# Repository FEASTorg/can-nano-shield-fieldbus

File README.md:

# can-nano-shield

A compact Arduino Nano shield with MCP2515 & TJA1051/3 for easy CAN bus integration. Work-in-progress.

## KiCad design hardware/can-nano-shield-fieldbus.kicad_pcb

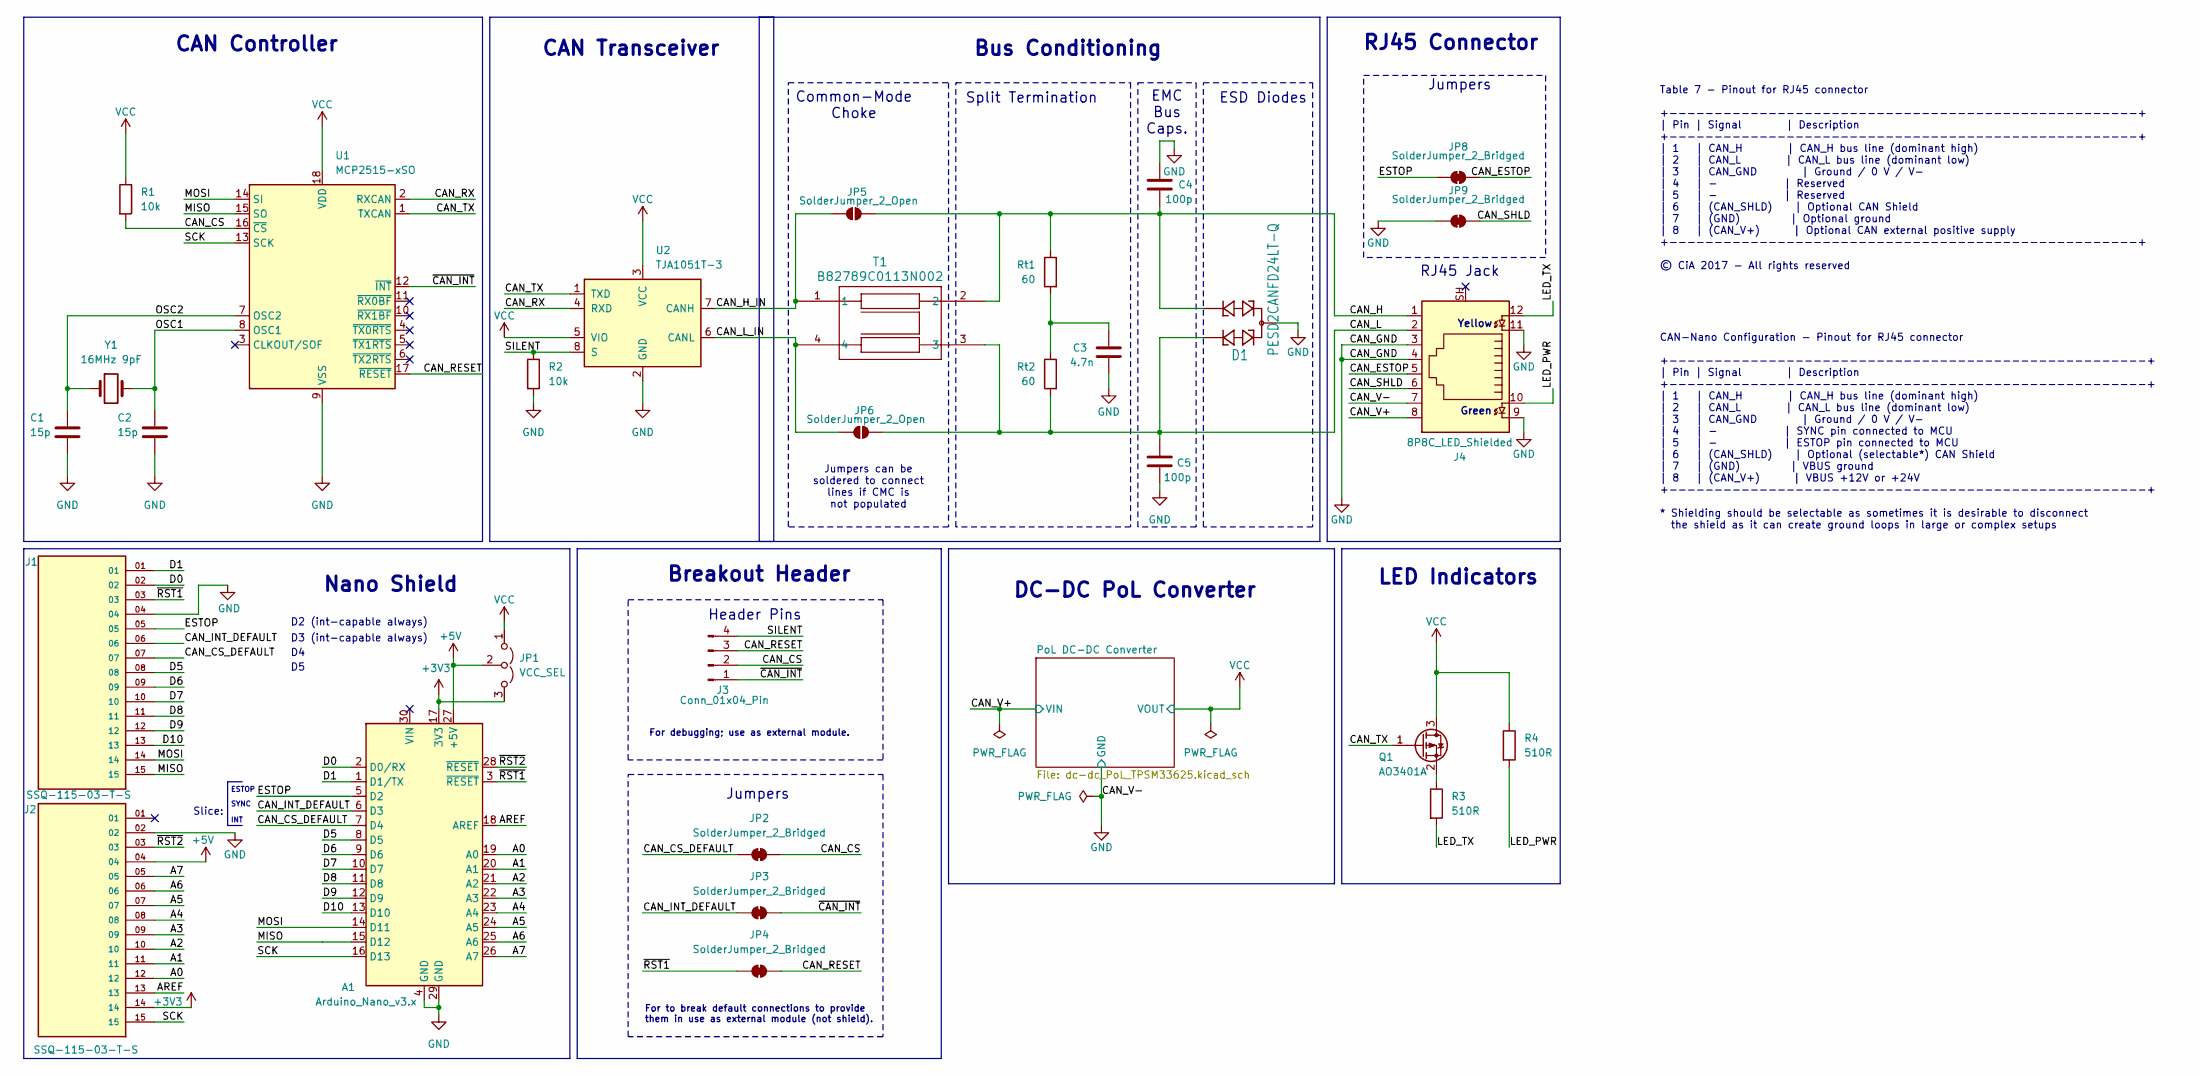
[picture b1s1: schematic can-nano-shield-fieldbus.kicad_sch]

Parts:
A1: Arduino_Nano_v3.x; Arduino_Nano
C1, C2: 15p; C_0603_1608Metric_Pad1.08x0.95mm_HandSolder
C3: 4.7n; C_0805_2012Metric_Pad1.18x1.45mm_HandSolder
C4, C5: 100p; C_0603_1608Metric_Pad1.08x0.95mm_HandSolder
D1: PESD2CANFD24LT-Q; TSOT-23
J1, J2: SSQ-115-03-T-S; SAMTEC_SSQ-115-03-T-S; PARTREV R
J3: Conn_01x04_Pin; PinHeader_1x04_P2.54mm_Horizontal
J4: 8P8C_LED_Shielded; 25015504-RJ45
JP1: VCC_SEL; SolderJumper-3_P1.3mm_Open_RoundedPad1.0x1.5mm
JP2, JP3, JP4, JP8, JP9: SolderJumper_2_Bridged; SolderJumper-2_P1.3mm_Bridged_RoundedPad1.0x1.5mm
JP5, JP6: SolderJumper_2_Open; SolderJumper-2_P1.3mm_Open_RoundedPad1.0x1.5mm
Q1: AO3401A; SOT-23
R1, R2: 10k; R_0805_2012Metric_Pad1.20x1.40mm_HandSolder
R3, R4: 510R; R_0805_2012Metric_Pad1.20x1.40mm_HandSolder
Rt1, Rt2: 60; R_0603_1608Metric_Pad0.98x0.95mm_HandSolder
T1: B82789C0113N002; SMT_13N002_TDK
U1: MCP2515-xSO; SOIC-18W_7.5x11.6mm_P1.27mm
U2: TJA1051T-3; SOIC-8_3.9x4.9mm_P1.27mm
Y1: 16MHz 9pF; Crystal_SMD_3225-4Pin_3.2x2.5mm_HandSoldering

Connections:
+3V3: A1.17 (3V3), J2.14, JP1.3 (B)
+5V: A1.27 (+5V), J2.04, JP1.2 (C)
/A0: A1.19 (A0), J2.12
/A1: A1.20 (A1), J2.11
/A2: A1.21 (A2), J2.10
/A3: A1.22 (A3), J2.09
/A4: A1.23 (A4), J2.08
/A5: A1.24 (A5), J2.07
/A6: A1.25 (A6), J2.06
/A7: A1.26 (A7), J2.05
/AREF: A1.18 (AREF), J2.13
/CAN_CS: J3.2, JP2.2 (B), R1.2, U1.16 (~CS)
/CAN_CS_DEFAULT: A1.7 (D4), J1.07, JP2.1 (A)
/CAN_ESTOP: J4.5, JP8.2 (B)
/CAN_H: C4.2, D1.1, J4.1, JP5.2 (B), Rt1.1, T1.2
/CAN_H_IN: JP5.1 (A), T1.1, U2.7 (CANH)
/CAN_INT_DEFAULT: A1.6 (D3), J1.06, JP3.1 (A)
/CAN_L: C5.1, D1.2, J4.2, JP6.2 (B), Rt2.2, T1.3
/CAN_L_IN: JP6.1 (A), T1.4, U2.6 (CANL)
/CAN_RESET: J3.3, JP4.2 (B), U1.17 (~RESET)
/CAN_RX: U1.2 (RXCAN), U2.4 (RXD)
/CAN_SHLD: J4.6, JP9.2 (B)
/CAN_TX: Q1.1 (G), U1.1 (TXCAN), U2.1 (TXD)
/CAN_V+: J4.8; also elsewhere on the board
/D0: A1.2 (D0/RX), J1.02
/D1: A1.1 (D1/TX), J1.01
/D5: A1.8 (D5), J1.08
/D6: A1.9 (D6), J1.09
/D7: A1.10 (D7), J1.10
/D8: A1.11 (D8), J1.11
/D9: A1.12 (D9), J1.12
/D10: A1.13 (D10), J1.13
/ESTOP: A1.5 (D2), J1.05, JP8.1 (A)
/LED_PWR: J4.10, R4.2
/LED_TX: J4.12, R3.2
/MISO: A1.15 (D12), J1.15, U1.15 (SO)
/MOSI: A1.14 (D11), J1.14, U1.14 (SI)
/OSC1: C2.1, U1.8 (OSC1), Y1.2
/OSC2: C1.1, U1.7 (OSC2), Y1.1
/RST1: A1.3 (~RESET), J1.03, JP4.1 (A)
/RST2: A1.28 (~RESET), J2.03
/SCK: A1.16 (D13), J2.15, U1.13 (SCK)
/SILENT: J3.4, R2.1, U2.8 (S)
/~CAN_INT: J3.1, JP3.2 (B), U1.12 (~INT)
GND: A1.4 (GND), A1.29 (GND), C1.2, C2.2, C3.2, C4.1, C5.2, D1.3, J1.04, J2.02, J4.3, J4.4, J4.7, J4.9, J4.11, JP9.1 (A), R2.2, U1.9 (VSS), U2.2 (GND); also elsewhere on the board
unnamed: C3.1, Rt1.2, Rt2.1
unnamed: Q1.2 (S), R3.1
VCC: JP1.1 (A), Q1.3 (D), R1.1, R4.1, U1.18 (VDD), U2.3 (VCC), U2.5 (VIO); also elsewhere on the board

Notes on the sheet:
Header Pins
EMC Bus Caps.
ESTOP
For debugging; use as external module.
Slice:
RJ45 Jack
Bus Conditioning
Breakout Header
INT
Jumpers
CAN Controller
ESD Diodes
For to break default connections to provide them in use as external module (not shield).
D3 (int-capable always)
Split Termination
SYNC
CAN Transceiver
RJ45 Connector
LED Indicators
CAN-Nano Configuration - Pinout for RJ45 connector +-----------------------------------------------------+ | Pin | Signal | Description +-----------------------------------------------------+ | 1 | CAN_H | CAN_H bus line (dominant high) | 2 | CAN_L | CAN_L bus line (dominant low) | 3 | CAN_GND | Gr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
Yellow
D2 (int-capable always)
DC-DC PoL Converter
Jumpers can be soldered to connect lines if CMC is not populated
Common-Mode Choke
Table 7 - Pinout for RJ45 connector +----------------------------------------------------+ | Pin | Signal | Description +----------------------------------------------------+ | 1 | CAN_H | CAN_H bus line (dominant high) | 2 | CAN_L | CAN_L bus line (dominant low) | 3 | CAN_GND | Ground / 0 V / V- |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
Nano Shield
Green

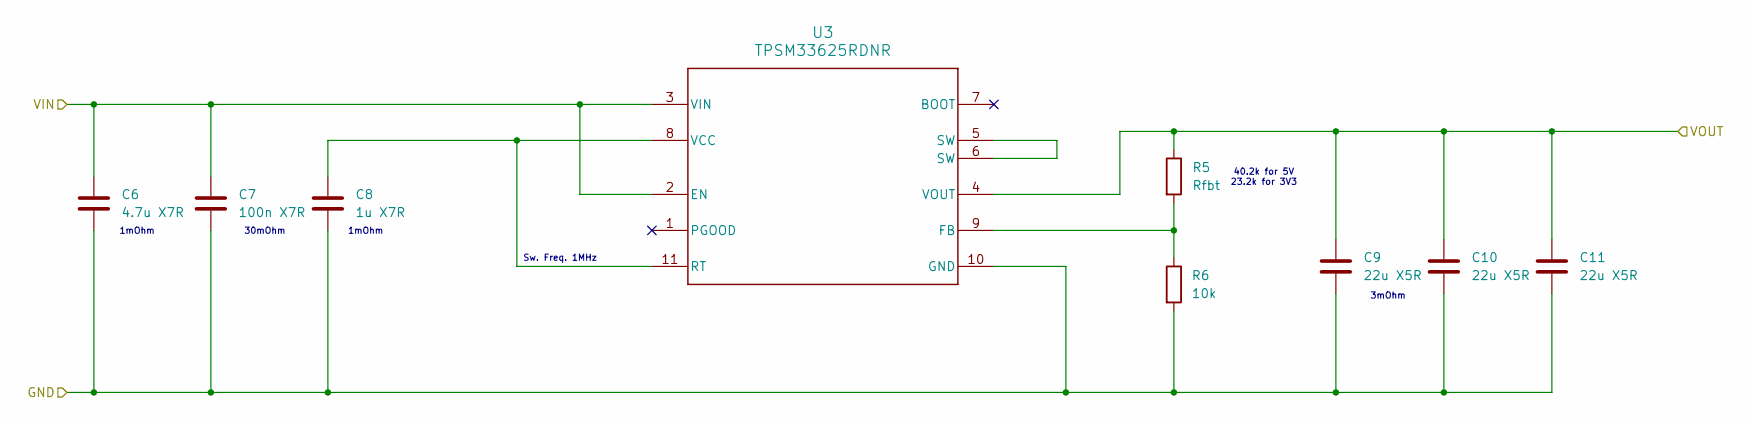
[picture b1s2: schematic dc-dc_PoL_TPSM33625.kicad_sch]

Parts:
C6: 4.7u X7R; C_1210_3225Metric_Pad1.33x2.70mm_HandSolder
C7: 100n X7R; C_0603_1608Metric_Pad1.08x0.95mm_HandSolder
C8: 1u X7R; C_0603_1608Metric_Pad1.08x0.95mm_HandSolder
C9, C10, C11: 22u X5R; C_0805_2012Metric_Pad1.18x1.45mm_HandSolder
R5: Rfbt; R_0603_1608Metric_Pad0.98x0.95mm_HandSolder
R6: 10k; R_0603_1608Metric_Pad0.98x0.95mm_HandSolder
U3: TPSM33625RDNR; CONV_TLVM23615RDNR

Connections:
/CAN_V+: C6.1, C7.1, U3.2 (EN), U3.3 (VIN), U3.3_1, U3.3_2; also elsewhere on the board
GND: C6.2, C7.2, C8.2, C9.2, C10.2, C11.2, R6.2, U3.10 (GND), U3.10_2, U3.10_3, U3.10_4, U3.10_5; also elsewhere on the board
unnamed: R5.2, R6.1, U3.9 (FB)
unnamed: C8.1, U3.8 (VCC), U3.11 (RT)
unnamed: U3.5 (SW), U3.5_1, U3.5_2, U3.5_3, U3.5_4, U3.5_5, U3.6 (SW), U3.6_1, U3.6_2
VCC: C9.1, C10.1, C11.1, R5.1, U3.4 (VOUT), U3.4_1, U3.4_2, U3.4_3, U3.4_4, U3.4_5; also elsewhere on the board

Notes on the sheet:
Sw. Freq. 1MHz
30mOhm
1mOhm
3mOhm
40.2k for 5V 23.2k for 3V3

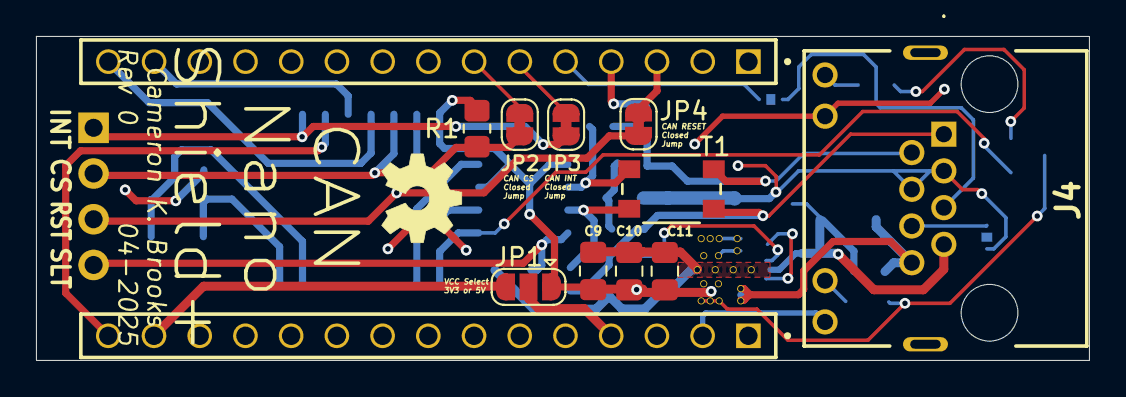
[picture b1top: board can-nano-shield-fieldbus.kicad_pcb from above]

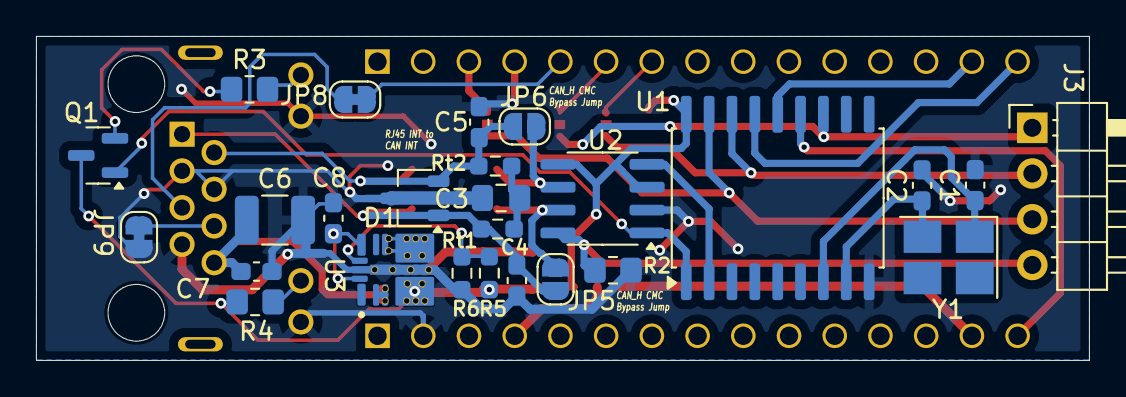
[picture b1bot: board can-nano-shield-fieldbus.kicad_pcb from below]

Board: 4 copper layers, 58.5 x 18.0 mm, 39 parts (26 on the bottom side), 33 nets.

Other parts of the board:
Ref**: Val**; OSHW_Logo_5mm

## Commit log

2025-03-30 added docs with readme for notes
2025-04-01 added image with cmc revision
2025-04-02 updated with cmc inductor + esd diode + emc caps on H L inputs
2025-04-22 added outputs
2025-04-22 updated parts dump
2025-04-25 fixed schem and corresponding hw
2025-04-25 update ouputs
2025-09-14 docs: clean up before split and pub to site
2025-09-14 minor: minor update before split of rj45
2025-09-14 initial commit of split
2025-09-14 remove index ignore
2025-09-14 docs: initial commit of docs using slice-infra
2025-09-14 ci: add docs pipeline for first deploy
2025-09-14 hardware: fix naming for consistency and reoutput
2025-09-14 move cmc revision pic to images and images to assets
2025-09-14 📄 KiBot index + board renders (auto)
2025-09-14 docs(ci): remove usage of inner copper layer images as pcb draw doesnt support
2025-09-14 rename: slice-infra --> bread-infra
2025-09-14 docs(config): aux links and color scheme (remote)
2025-09-23 enh: add inner layers to pcb pdf output from kibot
2026-04-20 refactor: org casing rename from 'FEASTorg' to 'feastorg'
2026-06-13 feat(grain): add grain.yaml manifest and validate CI

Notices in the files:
hardware/can-nano-shield-fieldbus.kicad_sch:
© CiA 2017 - All rights reserved
